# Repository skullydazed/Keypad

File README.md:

Darkstar Backlit Keypad
=======================

This is a KiCad project for my backlit 10-key. The goal is to design a keypad
for excel power-users.

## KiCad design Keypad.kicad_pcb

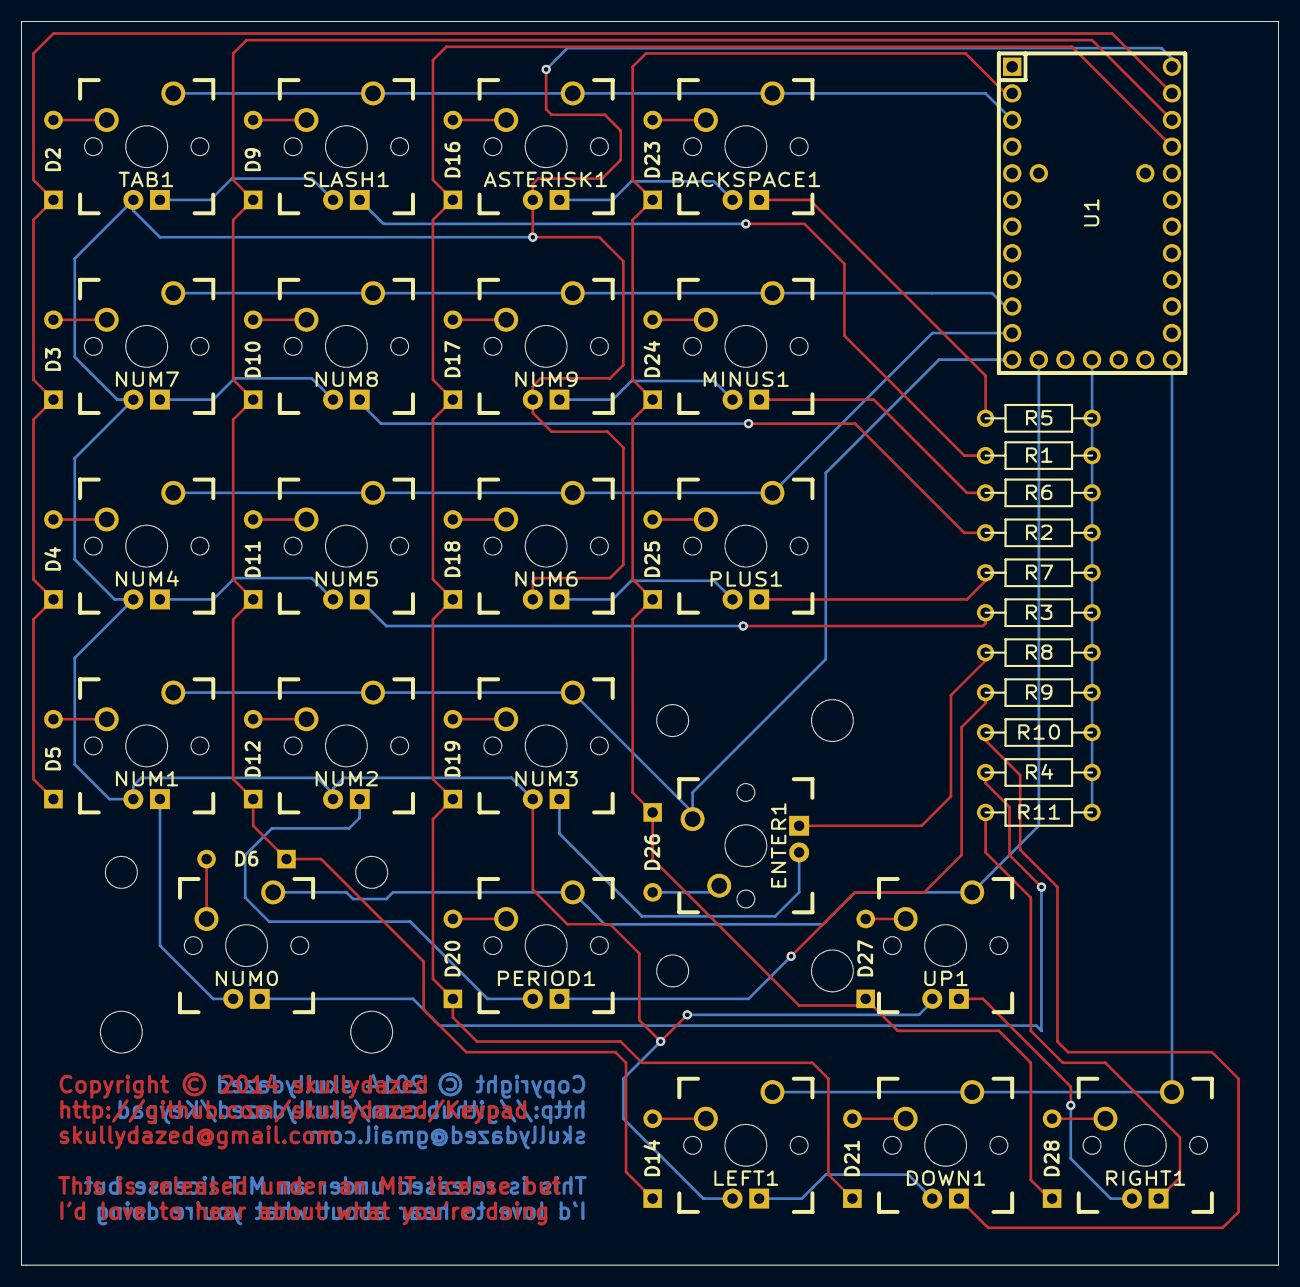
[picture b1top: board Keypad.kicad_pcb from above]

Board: 2 copper layers, 119.9 x 118.6 mm, 78 parts (0 on the bottom side), 56 nets.

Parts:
ASTERISK1: SW_PUSH; CHERRY_PCB_100H
BACKSPACE1: SW_PUSH; CHERRY_PCB_100H
D2, D3, D4, D5, D6, D9, D10, D11, D12, D14, D16, D17, D18, D19, D20, D21, D23, D24, D25, D26, D27, D28: DIODE; CHERRY_MX_DIODE
DOWN1: SW_PUSH; CHERRY_PCB_100H
ENTER1: SW_PUSH; CHERRY_PCB_200V
LED1, LED2, LED3, LED4, LED5, LED6, LED7, LED8, LED9, LED10, LED11, LED12, LED13, LED14, LED15, LED16, LED17, LED18, LED19, LED20, LED21, LED22: LED; CHERRY_MX_LED
LEFT1: SW_PUSH; CHERRY_PCB_100H
MINUS1: SW_PUSH; CHERRY_PCB_100H
NUM0: SW_PUSH; CHERRY_PCB_200H
NUM1, NUM2, NUM3, NUM4, NUM5, NUM6, NUM7, NUM8, NUM9: SW_PUSH; CHERRY_PCB_100H
PERIOD1: SW_PUSH; CHERRY_PCB_100H
PLUS1: SW_PUSH; CHERRY_PCB_100H
R1, R2, R3, R4, R5, R6, R7, R8, R9, R10, R11: 51Ω; RESISTOR
RIGHT1: SW_PUSH; CHERRY_PCB_100H
SLASH1: SW_PUSH; CHERRY_PCB_100H
TAB1: SW_PUSH; CHERRY_PCB_100H
U1: TEENSY2.0; TEENSY_2.0
UP1: SW_PUSH; CHERRY_PCB_100H

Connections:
+5v: LED1.1, LED3.1, LED5.1, LED7.1, LED9.1, LED11.1, LED13.1, LED15.1, LED17.1, LED19.1, LED21.1, U1.29
COLUMN1: D2.2, D3.2, D4.2, D5.2, U1.28
COLUMN2: D6.2, D9.2, D10.2, D11.2, D12.2, D14.2, U1.27
COLUMN3: D16.2, D17.2, D18.2, D19.2, D20.2, D21.2, U1.26
COLUMN4: D23.2, D24.2, D25.2, D26.2, D27.2, D28.2, U1.2
GND: R1.2, R2.2, R3.2, R4.2, R5.2, R6.2, R7.2, R8.2, R9.2, R10.2, R11.2, U1.15
unnamed: ASTERISK1.2, D16.1
unnamed: BACKSPACE1.2, D23.1
unnamed: D2.1, TAB1.2
unnamed: D3.1, NUM7.2
unnamed: D4.1, NUM4.2
unnamed: D5.1, NUM1.2
unnamed: D6.1, NUM0.2
unnamed: D9.1, SLASH1.2
unnamed: D10.1, NUM8.2
unnamed: D11.1, NUM5.2
unnamed: D12.1, NUM2.2
unnamed: D14.1, LEFT1.2
unnamed: D17.1, NUM9.2
unnamed: D18.1, NUM6.2
unnamed: D19.1, NUM3.2
unnamed: D20.1, PERIOD1.2
unnamed: D21.1, DOWN1.2
unnamed: D24.1, MINUS1.2
unnamed: D25.1, PLUS1.2
unnamed: D26.1, ENTER1.2
unnamed: D27.1, UP1.2
unnamed: D28.1, RIGHT1.2
unnamed: LED1.2, LED2.1
unnamed: LED2.2, R1.1
unnamed: LED3.2, LED4.1
unnamed: LED4.2, R2.1
unnamed: LED5.2, LED6.1
unnamed: LED6.2, R3.1
unnamed: LED7.2, LED8.1
unnamed: LED8.2, R4.1
unnamed: LED9.2, LED10.1
unnamed: LED10.2, R5.1
unnamed: LED11.2, LED12.1
unnamed: LED12.2, R6.1
unnamed: LED13.2, LED14.1
unnamed: LED14.2, R7.1
unnamed: LED15.2, LED16.1
unnamed: LED16.2, R8.1
unnamed: LED17.2, LED18.1
unnamed: LED18.2, R9.1
unnamed: LED19.2, LED20.1
unnamed: LED20.2, R10.1
unnamed: LED21.2, LED22.1
unnamed: LED22.2, R11.1
ROW1: ASTERISK1.1, BACKSPACE1.1, SLASH1.1, TAB1.1, U1.3
ROW2: MINUS1.1, NUM7.1, NUM8.1, NUM9.1, U1.10
ROW3: NUM4.1, NUM5.1, NUM6.1, PLUS1.1, U1.11
ROW4: ENTER1.1, NUM1.1, NUM2.1, NUM3.1, U1.12
ROW5: NUM0.1, PERIOD1.1, U1.13, UP1.1
ROW6: DOWN1.1, LEFT1.1, RIGHT1.1, U1.18

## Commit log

2014-11-04 Initial version of the darkstar keypad
2014-11-04 Adding images so people can see what it looks like

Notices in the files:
Keypad.kicad_pcb:
Copyright © 2014 skullydazed
This is released under an MIT license but I'd love to hear about what you're doing
